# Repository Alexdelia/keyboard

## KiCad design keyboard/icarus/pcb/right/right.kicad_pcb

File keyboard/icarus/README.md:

# icarus

Board 1: split, low profile, Hall effect (Gateron LP Magnetic Jade), wired USB-C, 4x6 + 4 thumb keys per half, one knob per half. Learning board, expected to fail.

All numbers are mm. Frame: left half, origin = middle column home key, x toward the thumbs, y down. Right half = mirror. "outer" = toward the pinky, "inner" = toward the other half.

## Files

| file | holds |
|---|---|
| `layout.json` | key positions (layout-fit tool, `tool/layout-fit/`), desk tilt 18 deg inward |
| `board.json` | knob, board outline, USB-C ports, plug, mounting, electronics zone, PCB layer stack |
| `parts.json` | parts with LCSC numbers |
| `channels.json` | key to mux channel, GPIO map |
| `placement.json` | pose of every non-key part |
| `pcb/`, `plate/`, `drawing/` | generated, never edit by hand (`pcb/` placement: `python -m kb.place`, routing: `python -m kb.route [left] [right]`; `drawing/`: `python -m kb.drawing`) |
| `fab/` | generated, git-ignored, JLCPCB order files per half: `<side>-gerbers.zip` (Gerbers + drill), `<side>-bom.csv`, `<side>-cpl.csv` (`python -m kb.fab`). CPL rotation corrections only for SOT-23, TSSOP, HRO USB-C (`JLC_ROTATION_DEG`); check every part in JLC's placement preview before paying |

## Board shape (`board.json`)

- outline hugs the keys: each keycap square (18.05) + 1.0 margin, inner corners radius 4, outer corners radius 2. Plate and bottom cover share it
- knob: rotary encoder with detents on BOTH halves, outermost column, number row
- host USB-C: on a 45 deg slope filling the step from the ring column's top outer corner to the pinky column's top edge, slope pushed out 1.5. Port centred on the slope, aimed 45 deg up and outward (27 deg on the desk)
- link USB-C: on an ear above the index column. Face starts at the middle column's top inner corner, square to an aim of 18 deg outward. The ear's far corner is a right angle, its edge runs straight to the index column's top inner corner. Port slid so the plug edge sits on that corner. Points straight up on the desk
- plug: assumed 12.4 wide, kept >= 1.0 from the board
- the 18 deg desk tilt is what turns the 18 deg link aim into straight up

## Stack

| layer | value |
|---|---|
| plate (transparent) | 1.2 thick, 1.30 above PCB |
| PCB (white, lead-free HASL) | 1.2, 4 copper layers, see below |
| parts | all on the PCB bottom, tallest USB-C 3.3 |
| bottom cover | 3.80 below PCB, needs feet >= 0.5 (plug hangs 0.13 below the cover) |

### PCB layers (`board.json` `pcb`)

JLCPCB 4-layer, 1.2 thick, impedance stack `JLC04121H-7628` (outer copper 1 oz, inner 0.5 oz). Layer thicknesses and dielectric constants are JLCPCB's for that stack; they add up to 1.15 with mask, the fab's nominal is 1.2. Copper finish lead-free HASL (`copperFinish`, KiCad name `HAL lead-free`).

| layer | kind | thickness | role |
|---|---|---|---|
| F.Mask | solder resist, er 3.8 | 0.01524 | |
| F.Cu | copper | 0.035 | signal |
| | prepreg NP-155F 7628, er 4.4 | 0.2104 | |
| In1.Cu | copper | 0.0152 | power: solid GND plane |
| | core NP-155F, er 4.36 | 0.6 | |
| In2.Cu | copper | 0.0152 | signal |
| | prepreg NP-155F 7628, er 4.4 | 0.2104 | |
| B.Cu | copper | 0.035 | signal |
| B.Mask | solder resist, er 3.8 | 0.01524 | |

- `kb.place` writes the layer count, layer roles (KiCad layer type) and this stackup into both boards
- a layer with `plane` gets one zone of that net covering the whole outline, regenerated and refilled on every run like Edge.Cuts. Copper keeps the board's edge clearance; the only gaps are clearances around other nets' holes and pads
- In1.Cu stays one unbroken GND plane under the analog lines, the muxes and the MCU

## Mounting

M2 wafer-head screws (head <= 0.8 tall), 6 per half, right = mirror of left:

- every four-way junction (four keycap corners meet), head hidden under the corners
- one hole in the thumb cluster, between two thumb keycaps where possible; its head may show
- T-junctions (two keycap corners and the side of a third), chosen so every key centre is <= 35 from a hole

Hole centres keep 3.1 from every plate cutout and the board edge, and 2.3 from sensors, their caps and the encoder parts. Check keycap bottom-out clearance once switches arrive; fallback is pan heads beside the keys.

## Electronics

MCU, flash, crystal, muxes and power parts fit inside the outline first. If they do not fit, the outline grows under the two outer columns down to the outermost thumb key.

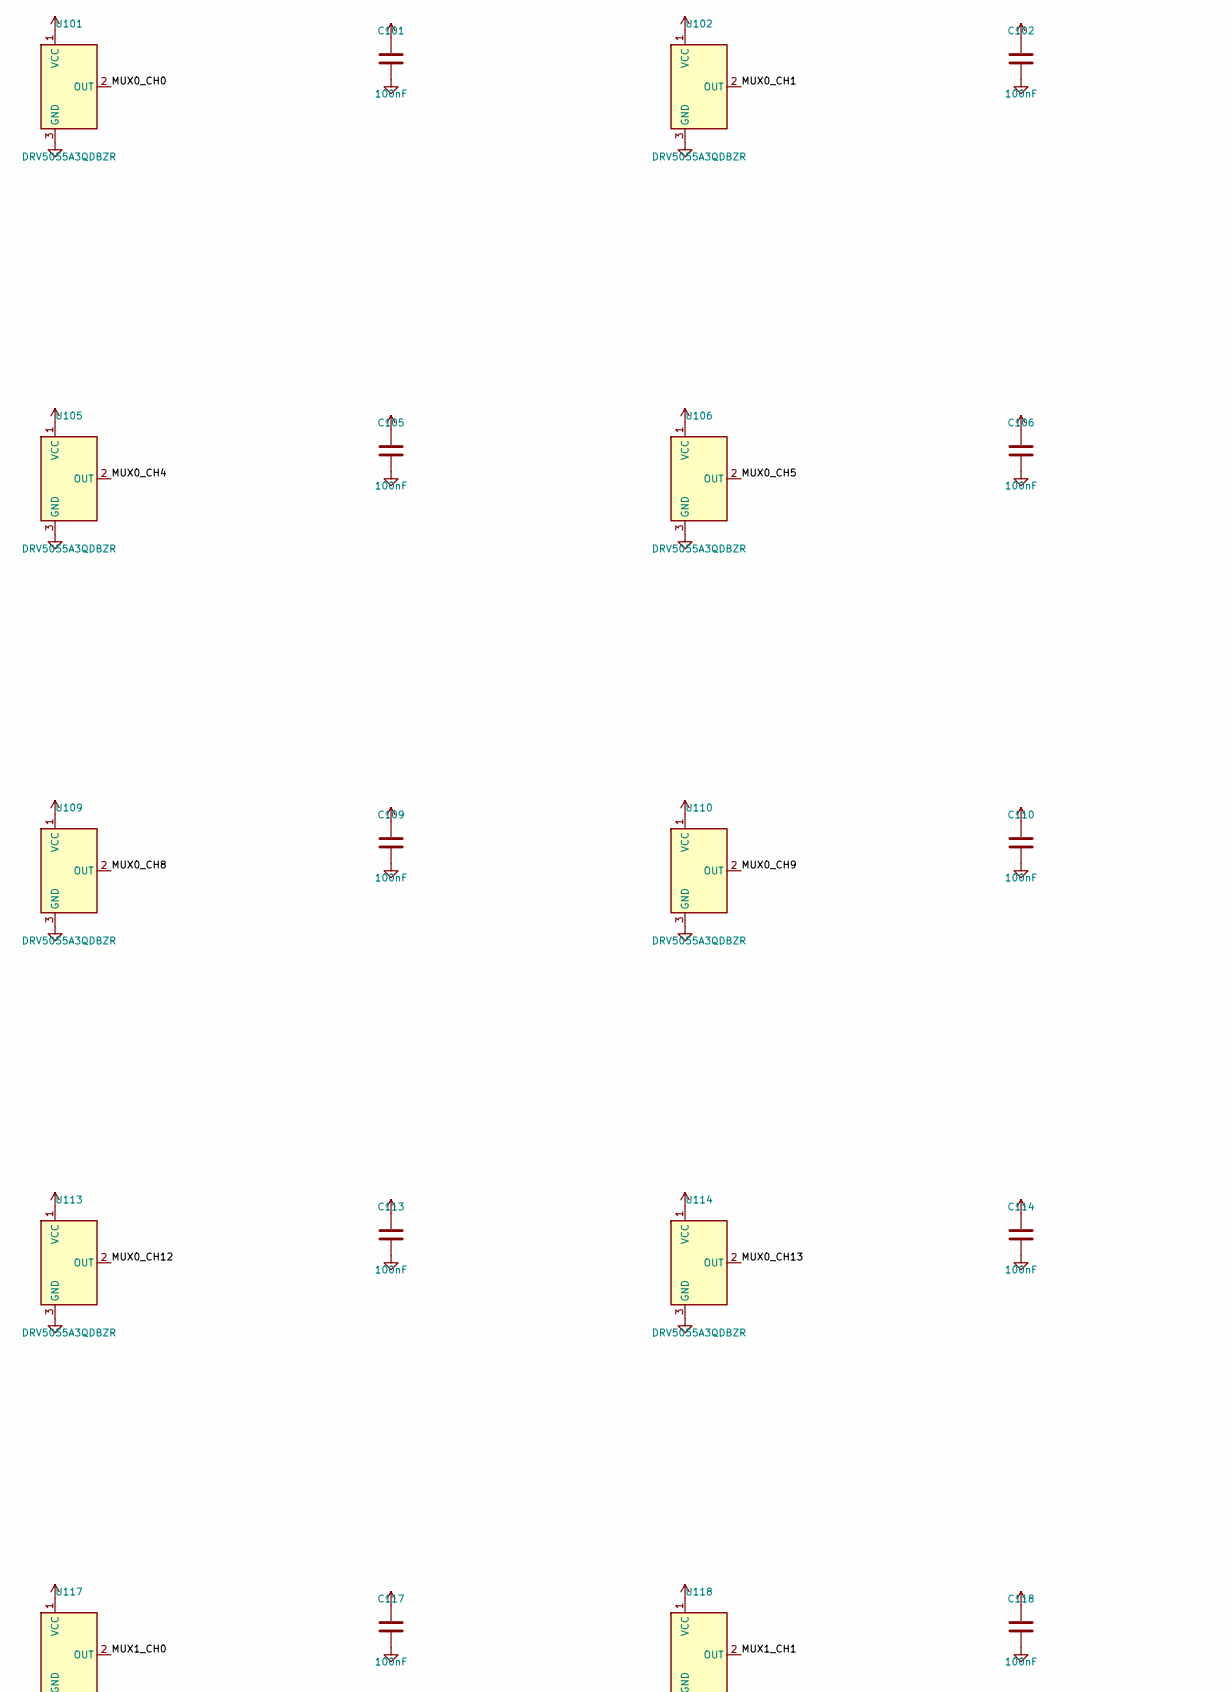
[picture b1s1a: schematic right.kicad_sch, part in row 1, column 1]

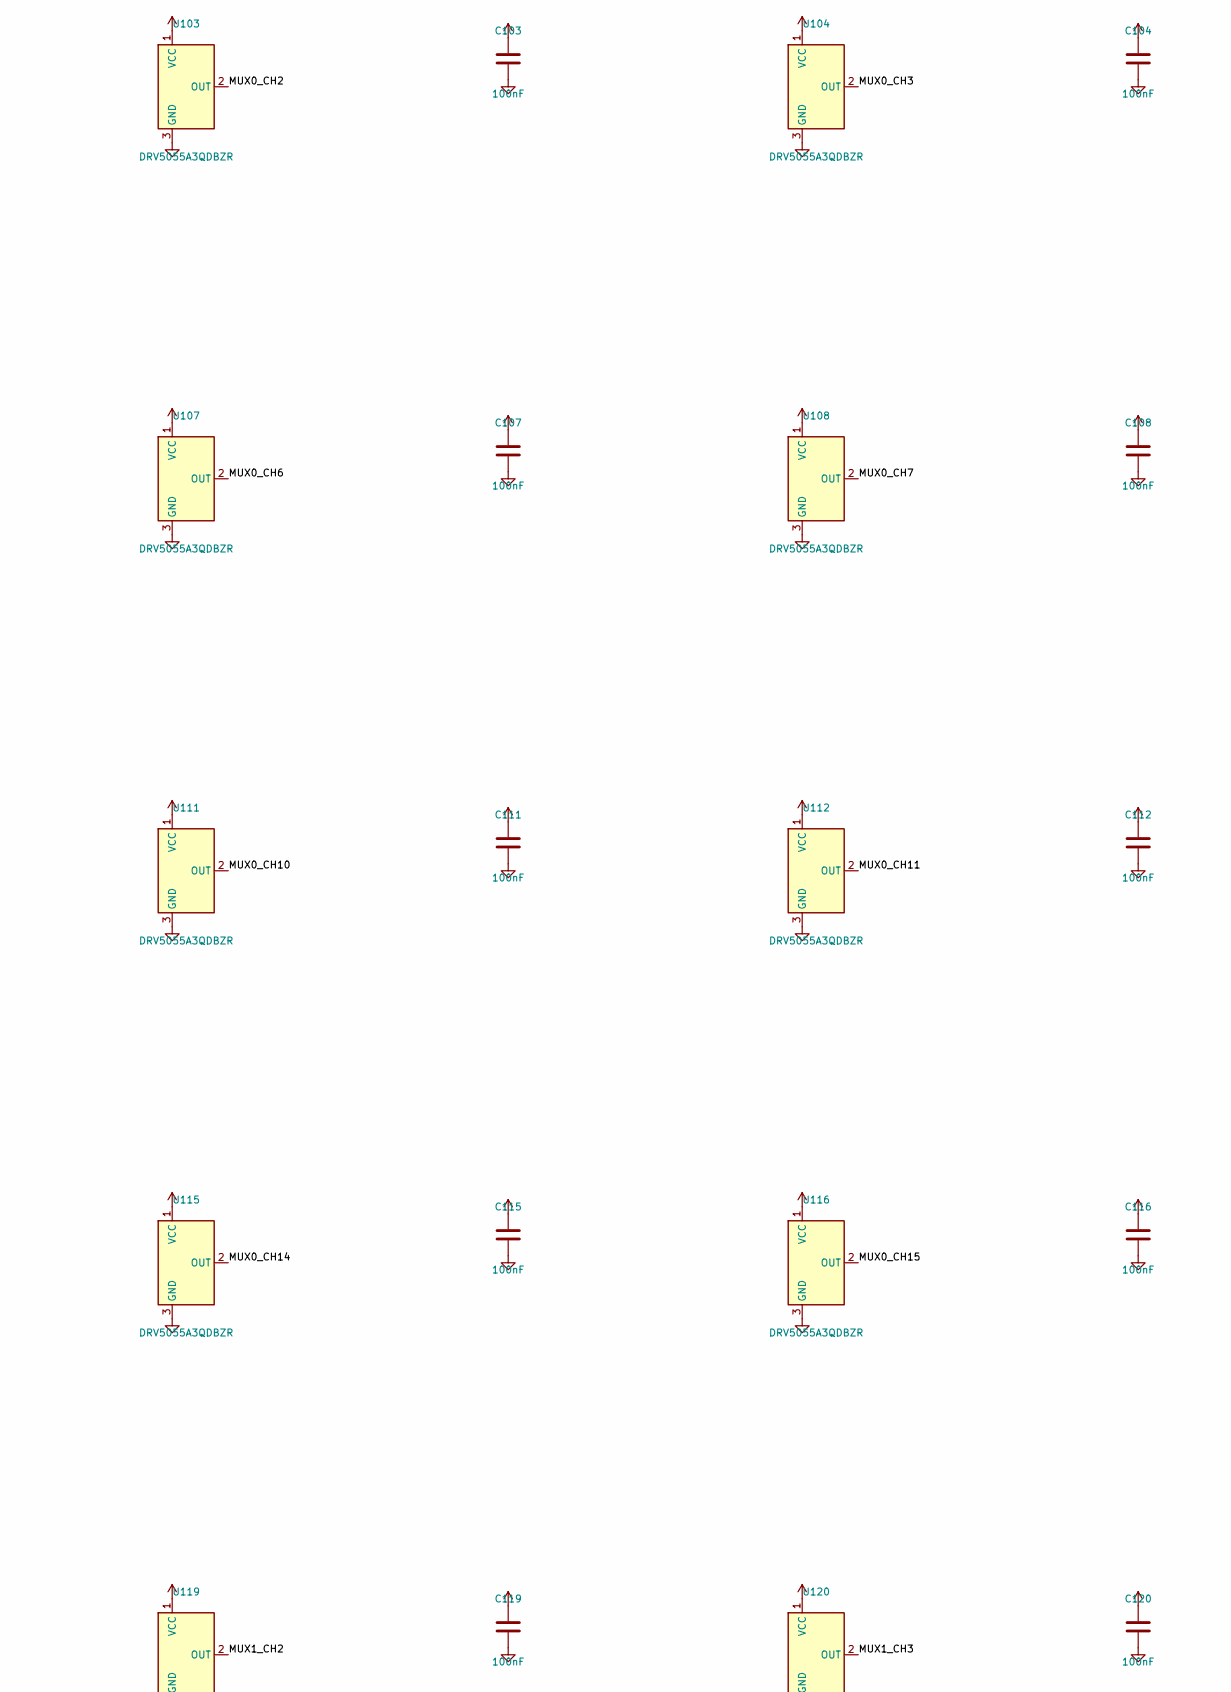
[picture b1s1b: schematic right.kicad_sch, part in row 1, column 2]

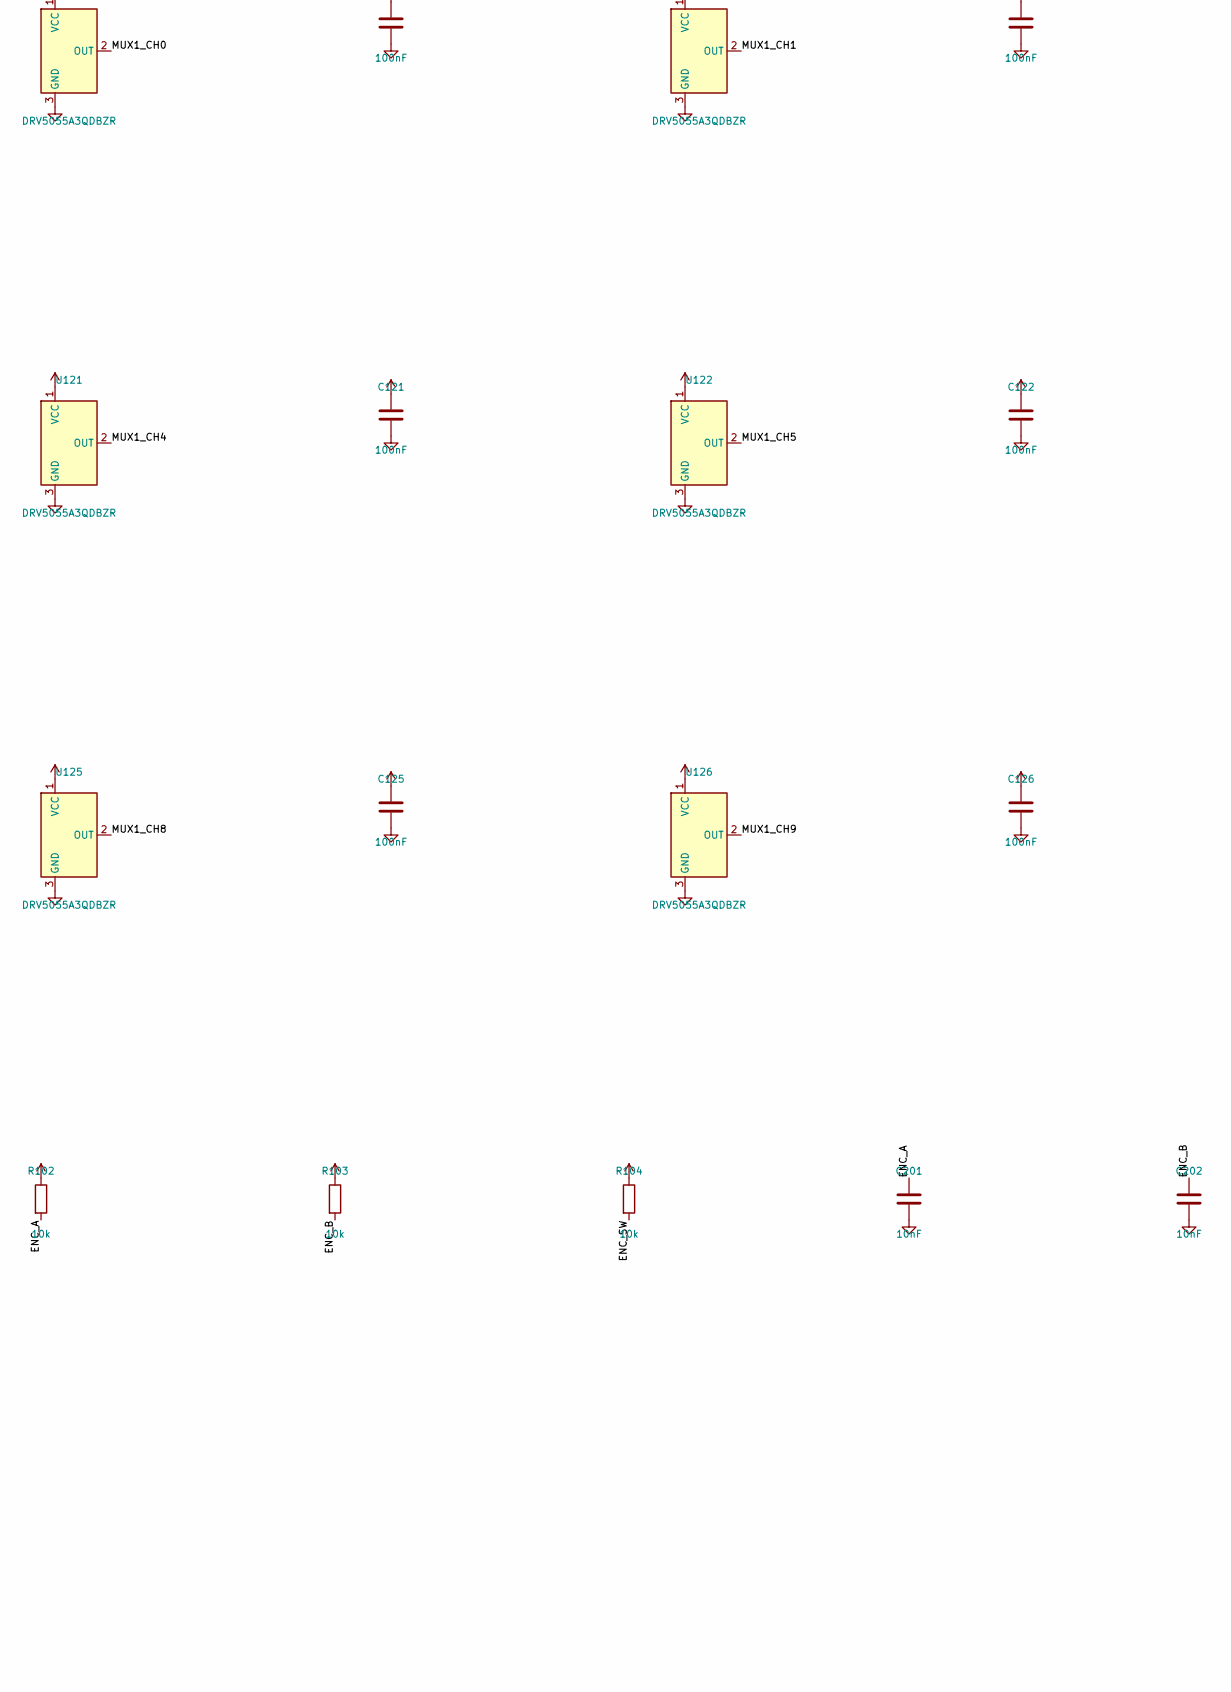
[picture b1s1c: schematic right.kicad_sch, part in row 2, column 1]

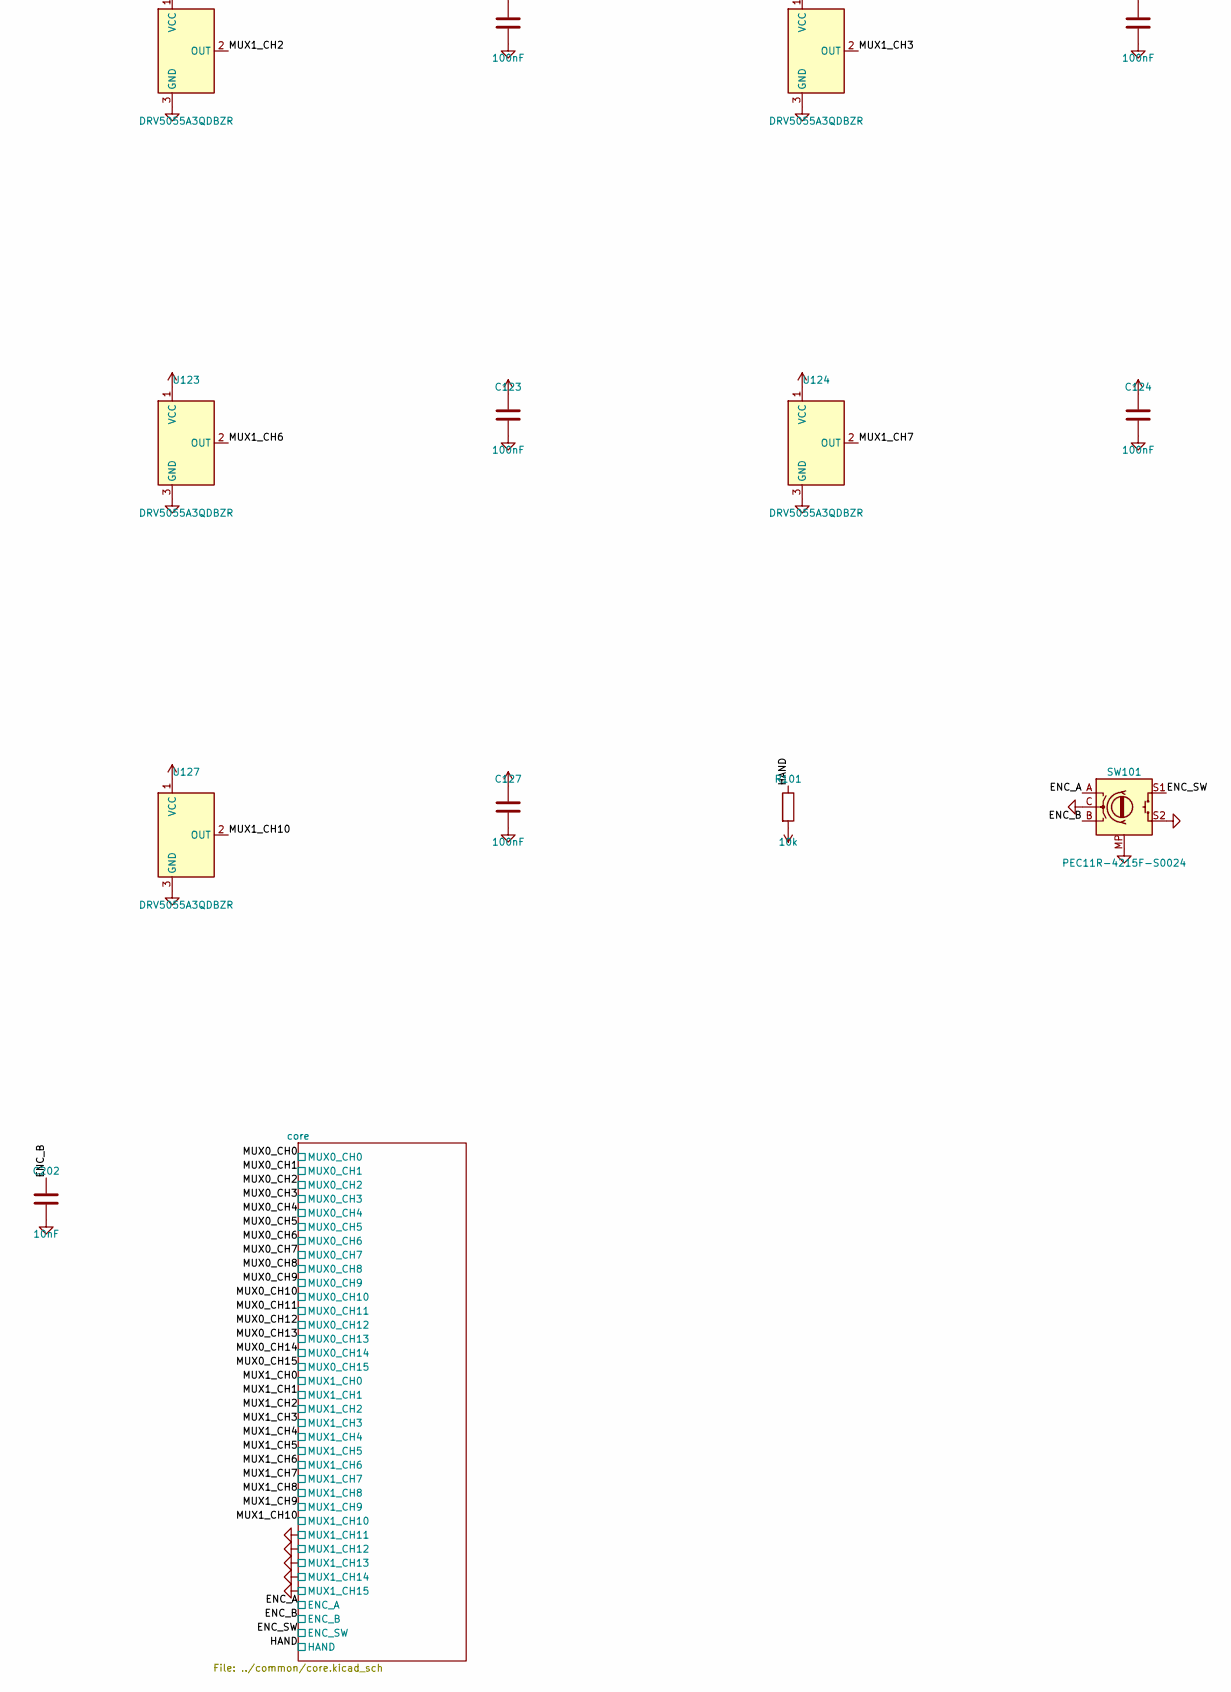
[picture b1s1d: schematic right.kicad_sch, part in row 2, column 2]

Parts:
C101, C102, C103, C104, C105, C106, C107, C108, C109, C110, C111, C112, C113, C114, C115, C116, C117, C118, C119, C120, C121, C122, C123, C124, C125, C126, C127: 100nF; C_0402_1005Metric; MPN CL05B104KO5NNNC; LCSC C1525
C201, C202: 10nF; C_0402_1005Metric; MPN CL05B103KB5NNNC; LCSC C15195
R101, R102, R103, R104: 10k; R_0402_1005Metric; MPN 0402WGF1002TCE; LCSC C25744
SW101: PEC11R-4215F-S0024; RotaryEncoder_Bourns_PEC11R-4xxxF-Sxxxx_Vertical; MPN PEC11R-4215F-S0024; LCSC C143790
U101, U102, U103, U104, U105, U106, U107, U108, U109, U110, U111, U112, U113, U114, U115, U116, U117, U118, U119, U120, U121, U122, U123, U124, U125, U126, U127: DRV5055A3QDBZR; SOT-23; MPN DRV5055A3QDBZR; LCSC C266128

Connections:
+3V3: C101.1, C102.1, C103.1, C104.1, C105.1, C106.1, C107.1, C108.1, C109.1, C110.1, C111.1, C112.1, C113.1, C114.1, C115.1, C116.1, C117.1, C118.1, C119.1, C120.1, C121.1, C122.1, C123.1, C124.1, C125.1, C126.1, C127.1, R101.2, R102.1, R103.1, R104.1, U101.1 (VCC), U102.1 (VCC), U103.1 (VCC), U104.1 (VCC), U105.1 (VCC), U106.1 (VCC), U107.1 (VCC), U108.1 (VCC), U109.1 (VCC), U110.1 (VCC), U111.1 (VCC), U112.1 (VCC), U113.1 (VCC), U114.1 (VCC), U115.1 (VCC), U116.1 (VCC), U117.1 (VCC), U118.1 (VCC), U119.1 (VCC), U120.1 (VCC), U121.1 (VCC), U122.1 (VCC), U123.1 (VCC), U124.1 (VCC), U125.1 (VCC), U126.1 (VCC), U127.1 (VCC); also elsewhere on the board
/ENC_A: C201.1, R102.2, SW101.A; also elsewhere on the board
/ENC_B: C202.1, R103.2, SW101.B; also elsewhere on the board
/ENC_SW: R104.2, SW101.S1; also elsewhere on the board
/HAND: R101.1; also elsewhere on the board
/MUX0_CH0: U101.2 (OUT); also elsewhere on the board
/MUX0_CH1: U102.2 (OUT); also elsewhere on the board
/MUX0_CH2: U103.2 (OUT); also elsewhere on the board
/MUX0_CH3: U104.2 (OUT); also elsewhere on the board
/MUX0_CH4: U105.2 (OUT); also elsewhere on the board
/MUX0_CH5: U106.2 (OUT); also elsewhere on the board
/MUX0_CH6: U107.2 (OUT); also elsewhere on the board
/MUX0_CH7: U108.2 (OUT); also elsewhere on the board
/MUX0_CH8: U109.2 (OUT); also elsewhere on the board
/MUX0_CH9: U110.2 (OUT); also elsewhere on the board
/MUX0_CH10: U111.2 (OUT); also elsewhere on the board
/MUX0_CH11: U112.2 (OUT); also elsewhere on the board
/MUX0_CH12: U113.2 (OUT); also elsewhere on the board
/MUX0_CH13: U114.2 (OUT); also elsewhere on the board
/MUX0_CH14: U115.2 (OUT); also elsewhere on the board
/MUX0_CH15: U116.2 (OUT); also elsewhere on the board
/MUX1_CH0: U117.2 (OUT); also elsewhere on the board
/MUX1_CH1: U118.2 (OUT); also elsewhere on the board
/MUX1_CH2: U119.2 (OUT); also elsewhere on the board
/MUX1_CH3: U120.2 (OUT); also elsewhere on the board
/MUX1_CH4: U121.2 (OUT); also elsewhere on the board
/MUX1_CH5: U122.2 (OUT); also elsewhere on the board
/MUX1_CH6: U123.2 (OUT); also elsewhere on the board
/MUX1_CH7: U124.2 (OUT); also elsewhere on the board
/MUX1_CH8: U125.2 (OUT); also elsewhere on the board
/MUX1_CH9: U126.2 (OUT); also elsewhere on the board
/MUX1_CH10: U127.2 (OUT); also elsewhere on the board
GND: C101.2, C102.2, C103.2, C104.2, C105.2, C106.2, C107.2, C108.2, C109.2, C110.2, C111.2, C112.2, C113.2, C114.2, C115.2, C116.2, C117.2, C118.2, C119.2, C120.2, C121.2, C122.2, C123.2, C124.2, C125.2, C126.2, C127.2, C201.2, C202.2, SW101.C, SW101.MP, SW101.S2, U101.3 (GND), U102.3 (GND), U103.3 (GND), U104.3 (GND), U105.3 (GND), U106.3 (GND), U107.3 (GND), U108.3 (GND), U109.3 (GND), U110.3 (GND), U111.3 (GND), U112.3 (GND), U113.3 (GND), U114.3 (GND), U115.3 (GND), U116.3 (GND), U117.3 (GND), U118.3 (GND), U119.3 (GND), U120.3 (GND), U121.3 (GND), U122.3 (GND), U123.3 (GND), U124.3 (GND), U125.3 (GND), U126.3 (GND), U127.3 (GND); also elsewhere on the board

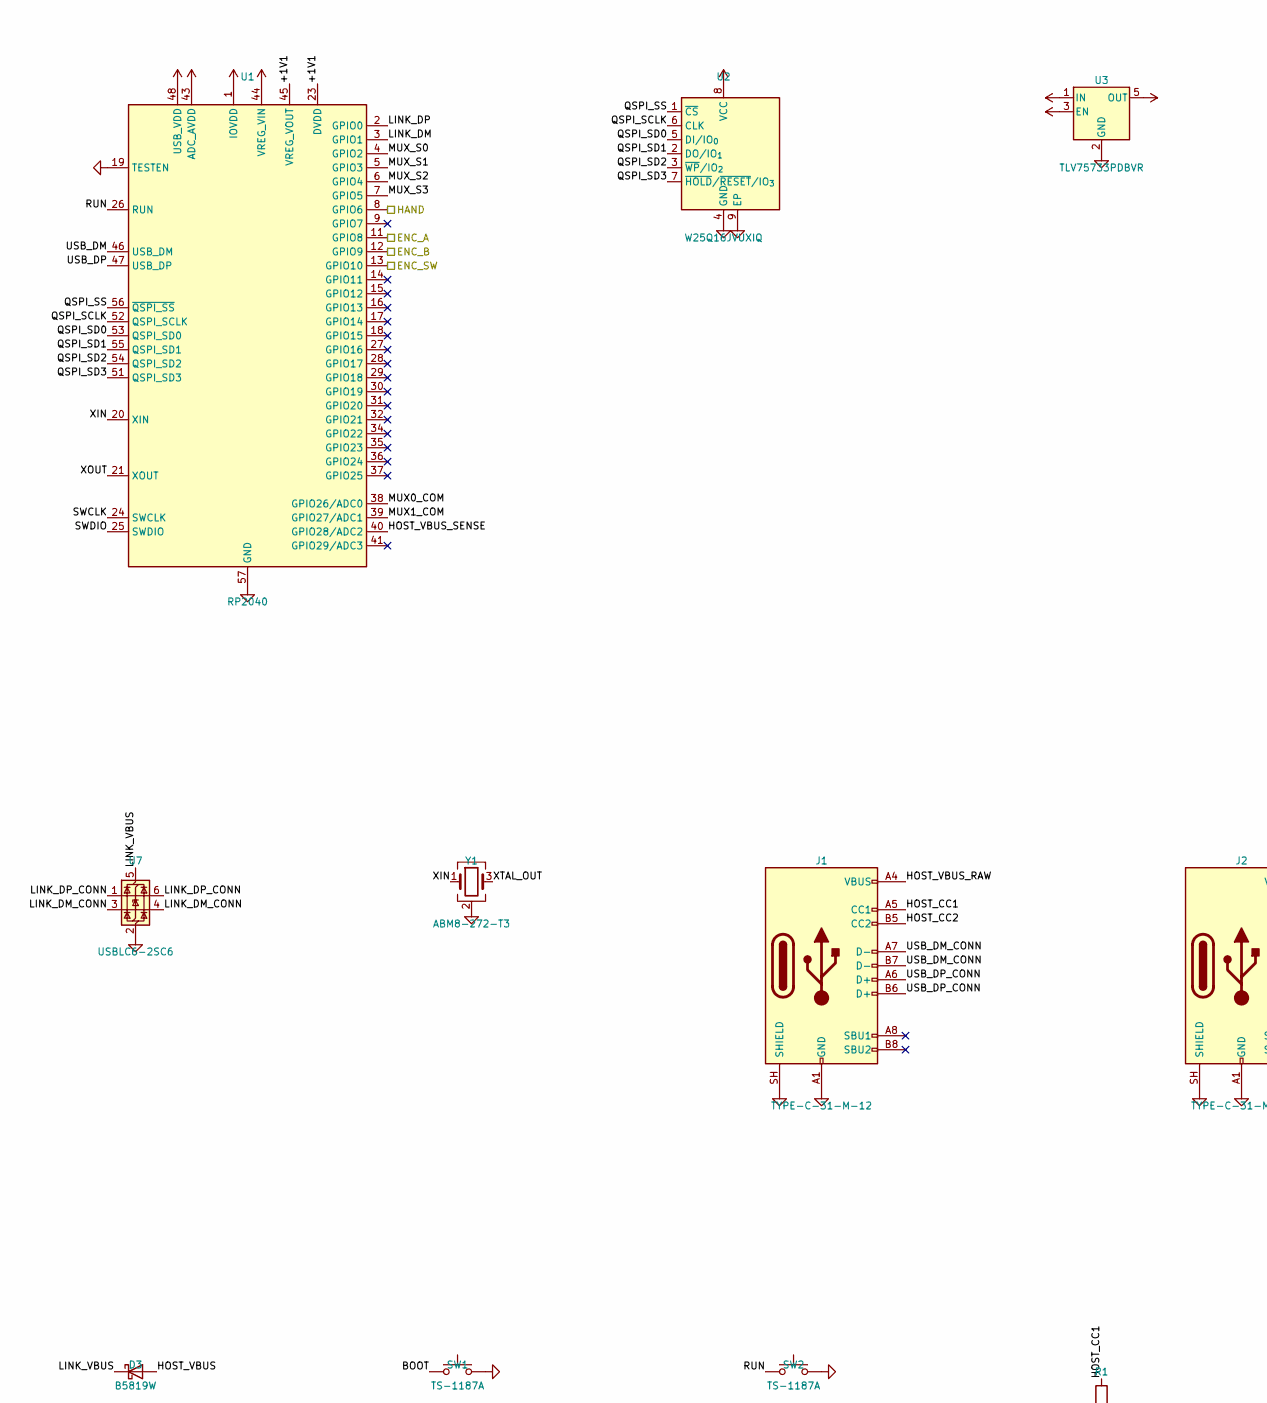
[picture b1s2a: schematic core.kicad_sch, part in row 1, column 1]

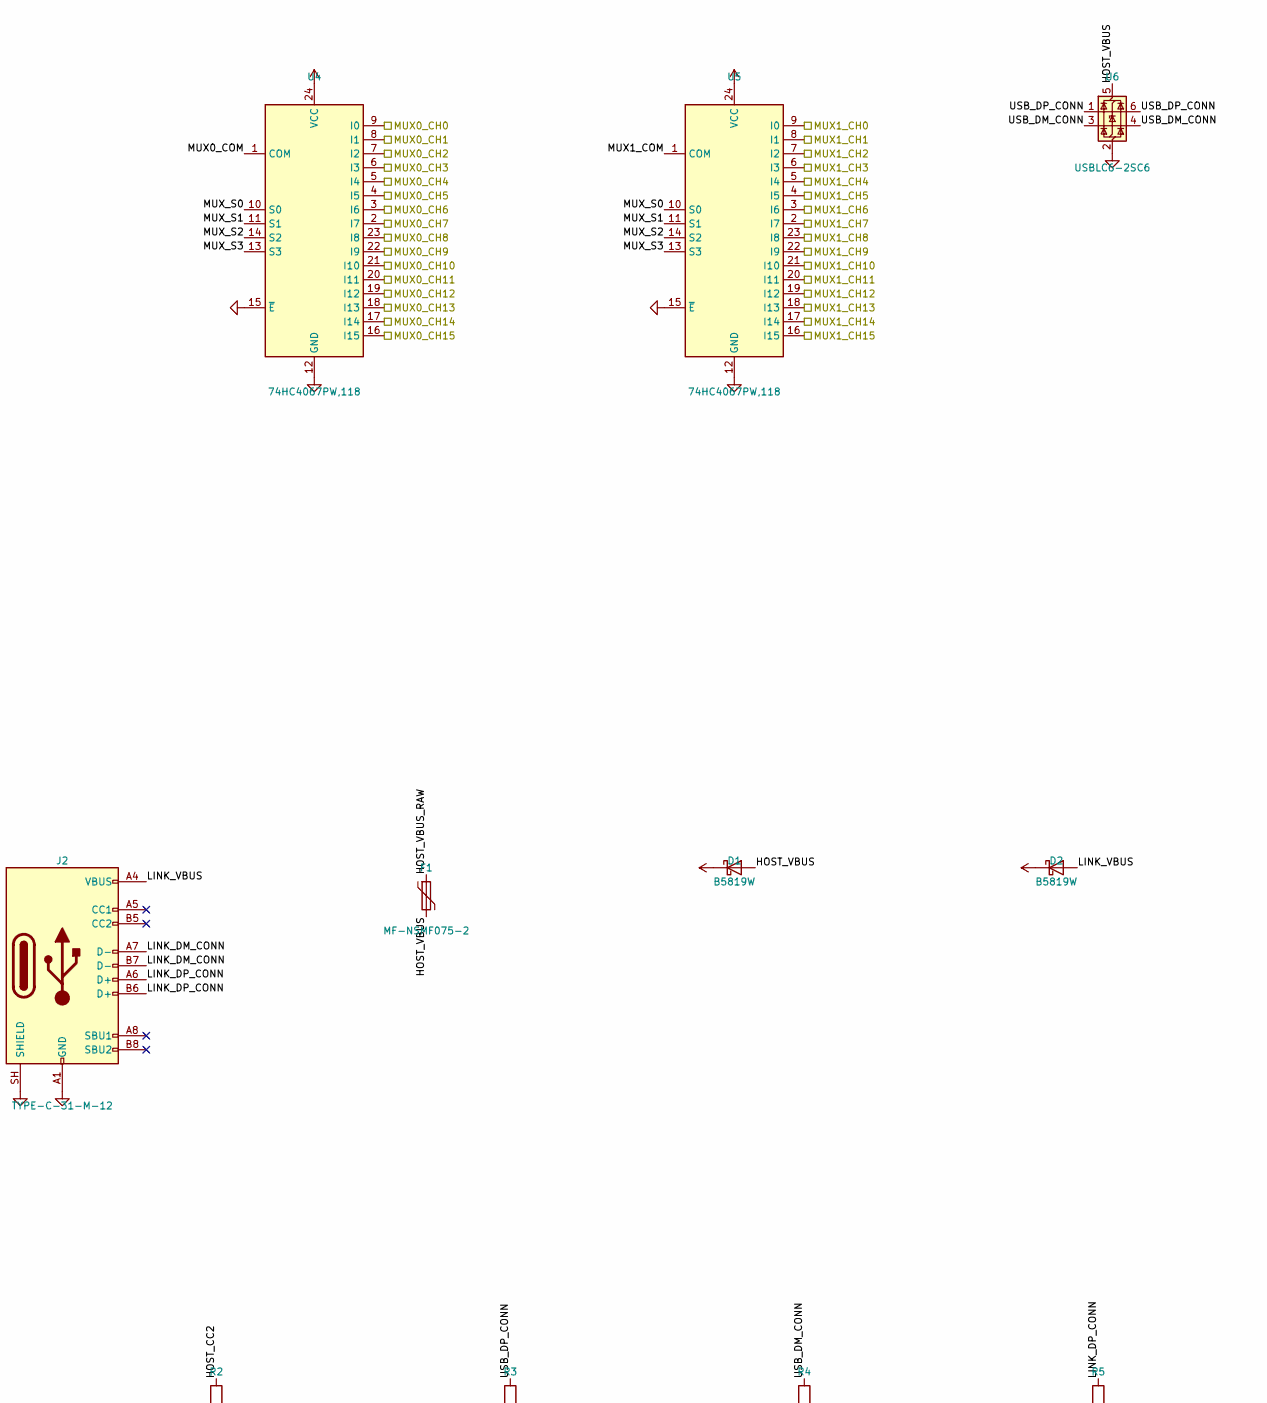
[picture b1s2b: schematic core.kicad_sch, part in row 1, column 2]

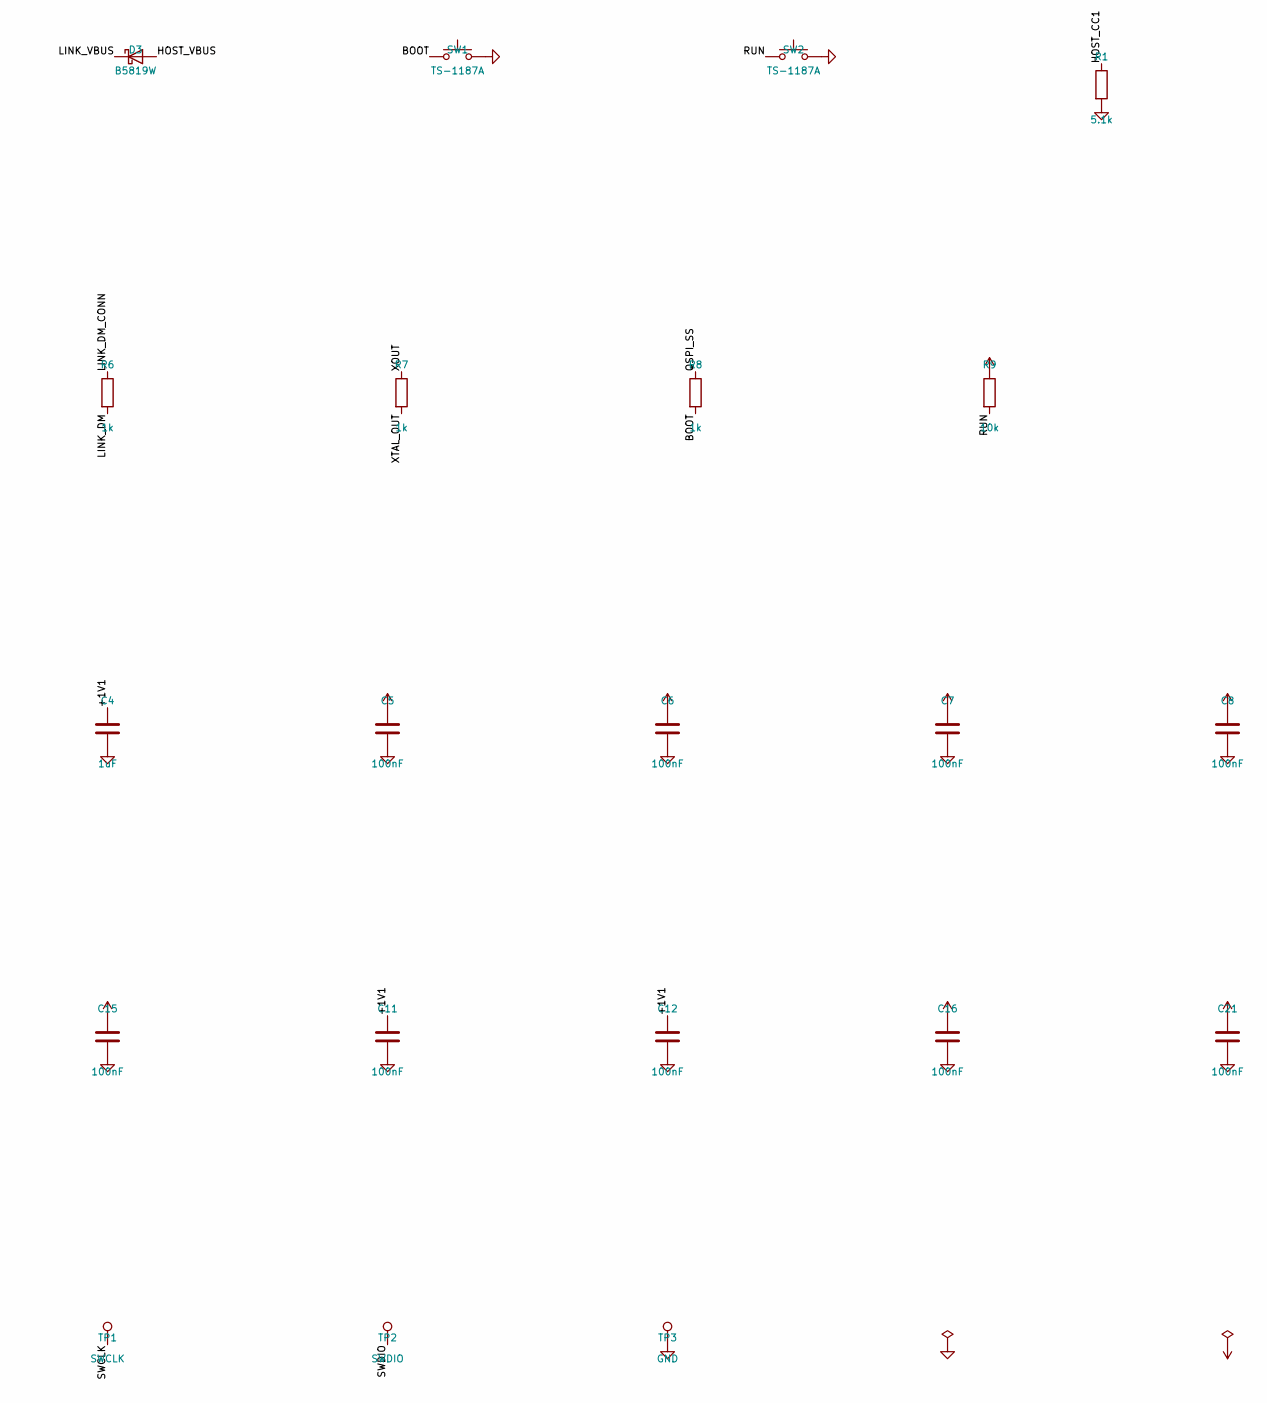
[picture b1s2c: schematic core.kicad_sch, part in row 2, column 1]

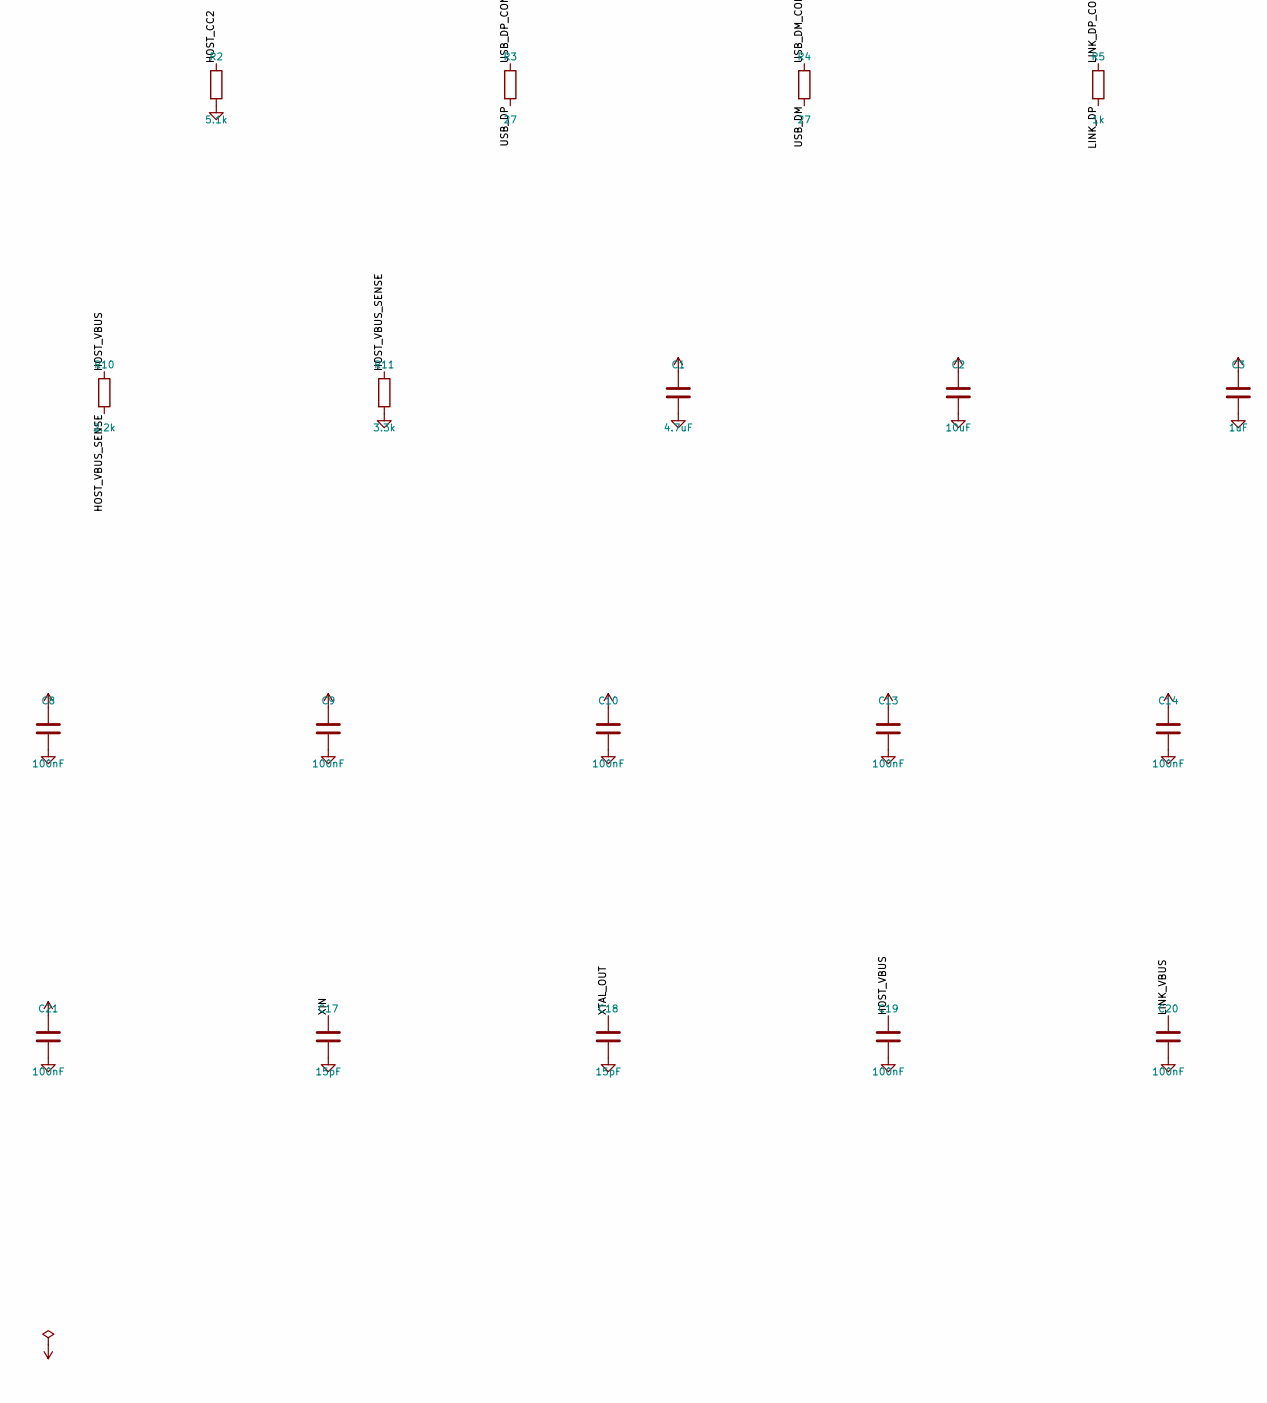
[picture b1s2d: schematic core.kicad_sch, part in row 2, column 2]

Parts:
C1: 4.7uF; C_0402_1005Metric; MPN CL05A475MP5NRNC; LCSC C23733
C2: 10uF; C_0402_1005Metric; MPN CL05A106MQ5NUNC; LCSC C15525
C3, C4: 1uF; C_0402_1005Metric; MPN CL05A105KA5NQNC; LCSC C52923
C5, C6, C7, C8, C9, C10, C11, C12, C13, C14, C15, C16, C19, C20, C21: 100nF; C_0402_1005Metric; MPN CL05B104KO5NNNC; LCSC C1525
C17, C18: 15pF; C_0402_1005Metric; MPN 0402CG150J500NT; LCSC C1548
D1, D2, D3: B5819W; D_SOD-123; MPN B5819W SL; LCSC C8598
F1: MF-NSMF075-2; Fuse_1206_3216Metric; MPN MF-NSMF075-2; LCSC C89653
J1, J2: TYPE-C-31-M-12; USB_C_Receptacle_HRO_TYPE-C-31-M-12; MPN TYPE-C-31-M-12; LCSC C165948
R1, R2: 5.1k; R_0402_1005Metric; MPN 0402WGF5101TCE; LCSC C25905
R3, R4: 27; R_0402_1005Metric; MPN 0402WGF270JTCE; LCSC C25100
R5, R6, R7, R8: 1k; R_0402_1005Metric; MPN 0402WGF1001TCE; LCSC C11702
R9: 10k; R_0402_1005Metric; MPN 0402WGF1002TCE; LCSC C25744
R10: 2.2k; R_0402_1005Metric; MPN 0402WGF2201TCE; LCSC C25879
R11: 3.3k; R_0402_1005Metric; MPN 0402WGF3301TCE; LCSC C25890
SW1, SW2: TS-1187A; SW_Push_1P1T_XKB_TS-1187A; MPN TS-1187A-B-A-B; LCSC C318884
TP1: SWCLK; TestPoint_Pad_D1.0mm
TP2: SWDIO; TestPoint_Pad_D1.0mm
TP3: GND; TestPoint_Pad_D1.0mm
U1: RP2040; QFN-56-1EP_7x7mm_P0.4mm_EP3.2x3.2mm; MPN RP2040; LCSC C2040
U2: W25Q16JVUXIQ; Winbond_USON-8-1EP_3x2mm_P0.5mm_EP0.2x1.6mm; MPN W25Q16JVUXIQ; LCSC C2843335
U3: TLV75733PDBVR; SOT-23-5; MPN TLV75733PDBVR; LCSC C485517
U4, U5: 74HC4067PW,118; TSSOP-24_4.4x7.8mm_P0.65mm; MPN 74HC4067PW,118; LCSC C179326
U6, U7: USBLC6-2SC6; SOT-23-6; MPN USBLC6-2SC6; LCSC C7519
Y1: ABM8-272-T3; Crystal_SMD_3225-4Pin_3.2x2.5mm; MPN ABM8-272-T3; LCSC C20625731

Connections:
+3V3: C2.1, C3.1, C5.1, C6.1, C7.1, C8.1, C9.1, C10.1, C13.1, C14.1, C15.1, C16.1, C21.1, R9.1, U1.1 (IOVDD), U1.10 (IOVDD), U1.22 (IOVDD), U1.33 (IOVDD), U1.42 (IOVDD), U1.43 (ADC_AVDD), U1.44 (VREG_VIN), U1.48 (USB_VDD), U1.49 (IOVDD), U2.8 (VCC), U3.5 (OUT), U4.24 (VCC), U5.24 (VCC); also elsewhere on the board
+5V: C1.1, D1.1 (K), D2.1 (K), U3.1 (IN), U3.3 (EN)
/ENC_A: U1.11 (GPIO8); also elsewhere on the board
/ENC_B: U1.12 (GPIO9); also elsewhere on the board
/ENC_SW: U1.13 (GPIO10); also elsewhere on the board
/HAND: U1.8 (GPIO6); also elsewhere on the board
/MUX0_CH0: U4.9 (I0); also elsewhere on the board
/MUX0_CH1: U4.8 (I1); also elsewhere on the board
/MUX0_CH2: U4.7 (I2); also elsewhere on the board
/MUX0_CH3: U4.6 (I3); also elsewhere on the board
/MUX0_CH4: U4.5 (I4); also elsewhere on the board
/MUX0_CH5: U4.4 (I5); also elsewhere on the board
/MUX0_CH6: U4.3 (I6); also elsewhere on the board
/MUX0_CH7: U4.2 (I7); also elsewhere on the board
/MUX0_CH8: U4.23 (I8); also elsewhere on the board
/MUX0_CH9: U4.22 (I9); also elsewhere on the board
/MUX0_CH10: U4.21 (I10); also elsewhere on the board
/MUX0_CH11: U4.20 (I11); also elsewhere on the board
/MUX0_CH12: U4.19 (I12); also elsewhere on the board
/MUX0_CH13: U4.18 (I13); also elsewhere on the board
/MUX0_CH14: U4.17 (I14); also elsewhere on the board
/MUX0_CH15: U4.16 (I15); also elsewhere on the board
/MUX1_CH0: U5.9 (I0); also elsewhere on the board
/MUX1_CH1: U5.8 (I1); also elsewhere on the board
/MUX1_CH2: U5.7 (I2); also elsewhere on the board
/MUX1_CH3: U5.6 (I3); also elsewhere on the board
/MUX1_CH4: U5.5 (I4); also elsewhere on the board
/MUX1_CH5: U5.4 (I5); also elsewhere on the board
/MUX1_CH6: U5.3 (I6); also elsewhere on the board
/MUX1_CH7: U5.2 (I7); also elsewhere on the board
/MUX1_CH8: U5.23 (I8); also elsewhere on the board
/MUX1_CH9: U5.22 (I9); also elsewhere on the board
/MUX1_CH10: U5.21 (I10); also elsewhere on the board
/core/+1V1: C4.1, C11.1, C12.1, U1.23 (DVDD), U1.45 (VREG_VOUT), U1.50 (DVDD)
/core/BOOT: R8.2, SW1.1
/core/HOST_CC1: J1.A5 (CC1), R1.1
/core/HOST_CC2: J1.B5 (CC2), R2.1
/core/HOST_VBUS: C19.1, D1.2 (A), D3.2 (A), F1.2, R10.1, U6.5 (VBUS)
/core/HOST_VBUS_RAW: F1.1, J1.A4 (VBUS), J1.A9 (VBUS), J1.B4 (VBUS), J1.B9 (VBUS)
/core/HOST_VBUS_SENSE: R10.2, R11.1, U1.40 (GPIO28/ADC2)
/core/LINK_DM: R6.2, U1.3 (GPIO1)
/core/LINK_DM_CONN: J2.A7 (D-), J2.B7 (D-), R6.1, U7.3 (I/O2), U7.4 (I/O2)
/core/LINK_DP: R5.2, U1.2 (GPIO0)
/core/LINK_DP_CONN: J2.A6 (D+), J2.B6 (D+), R5.1, U7.1 (I/O1), U7.6 (I/O1)
/core/LINK_VBUS: C20.1, D2.2 (A), D3.1 (K), J2.A4 (VBUS), J2.A9 (VBUS), J2.B4 (VBUS), J2.B9 (VBUS), U7.5 (VBUS)
/core/MUX0_COM: U1.38 (GPIO26/ADC0), U4.1 (COM)
/core/MUX1_COM: U1.39 (GPIO27/ADC1), U5.1 (COM)
/core/MUX_S0: U1.4 (GPIO2), U4.10 (S0), U5.10 (S0)
/core/MUX_S1: U1.5 (GPIO3), U4.11 (S1), U5.11 (S1)
/core/MUX_S2: U1.6 (GPIO4), U4.14 (S2), U5.14 (S2)
/core/MUX_S3: U1.7 (GPIO5), U4.13 (S3), U5.13 (S3)
/core/QSPI_SCLK: U1.52 (QSPI_SCLK), U2.6 (CLK)
/core/QSPI_SD0: U1.53 (QSPI_SD0), U2.5 (DI/IO_{0})
/core/QSPI_SD1: U1.55 (QSPI_SD1), U2.2 (DO/IO_{1})
/core/QSPI_SD2: U1.54 (QSPI_SD2), U2.3 (~WP/IO_{2})
/core/QSPI_SD3: U1.51 (QSPI_SD3), U2.7 (~HOLD/~RESET/IO_{3})
/core/QSPI_SS: R8.1, U1.56 (~QSPI_SS), U2.1 (~CS)
/core/RUN: R9.2, SW2.1, U1.26 (RUN)
/core/SWCLK: TP1.1, U1.24 (SWCLK)
/core/SWDIO: TP2.1, U1.25 (SWDIO)
/core/USB_DM: R4.2, U1.46 (USB_DM)
/core/USB_DM_CONN: J1.A7 (D-), J1.B7 (D-), R4.1, U6.3 (I/O2), U6.4 (I/O2)
/core/USB_DP: R3.2, U1.47 (USB_DP)
/core/USB_DP_CONN: J1.A6 (D+), J1.B6 (D+), R3.1, U6.1 (I/O1), U6.6 (I/O1)
/core/XIN: C17.1, U1.20 (XIN), Y1.1
/core/XOUT: R7.1, U1.21 (XOUT)
/core/XTAL_OUT: C18.1, R7.2, Y1.3
GND: C1.2, C2.2, C3.2, C4.2, C5.2, C6.2, C7.2, C8.2, C9.2, C10.2, C11.2, C12.2, C13.2, C14.2, C15.2, C16.2, C17.2, C18.2, C19.2, C20.2, C21.2, J1.A1 (GND), J1.A12 (GND), J1.B1 (GND), J1.B12 (GND), J1.SH (SHIELD), J2.A1 (GND), J2.A12 (GND), J2.B1 (GND), J2.B12 (GND), J2.SH (SHIELD), R1.2, R2.2, R11.2, SW1.2, SW2.2, TP3.1, U1.19 (TESTEN), U1.57 (GND), U2.4 (GND), U2.9 (EP), U3.2 (GND), U4.12 (GND), U4.15 (~E), U5.12 (GND), U5.15 (~E), U5.16 (I15), U5.17 (I14), U5.18 (I13), U5.19 (I12), U5.20 (I11), U6.2 (GND), U7.2 (GND), Y1.2 (G), Y1.4 (G); also elsewhere on the board
